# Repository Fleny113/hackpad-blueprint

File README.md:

# Fleny's Hackpad

Repo containing the files for my HackPad made for Blueprint by Hack Club.

It has a rotary encoder for volume, 4 keys for media control with an extra one for anything that might be useful and a OLED to show information about the media.

This is my first time doing any PCB and CAD work, so hopefully there isn't a mess

## BOM

- 1x Seeed Studio XIAO RP2040
- 1x 0.91 inch OLED displays
- 1x EC11 Rotary encoder
- 2x SK6812 MINI-E LEDs
- 5x MX-Style switches
- 8x M3x5mx4mm heatset inserts
- 8x M3 Screws

## Images

### Schematic

The schematic for the hackpad

### PCB

The PCB of the hackpad

<details>
<summary>PCB without the zones shown</summary>

The PCB but with the zones hidden as I find them confusing when searching the traces

</details>

### CAD

#### Entire assembly:

#### Only the body:

#### Only the lid:

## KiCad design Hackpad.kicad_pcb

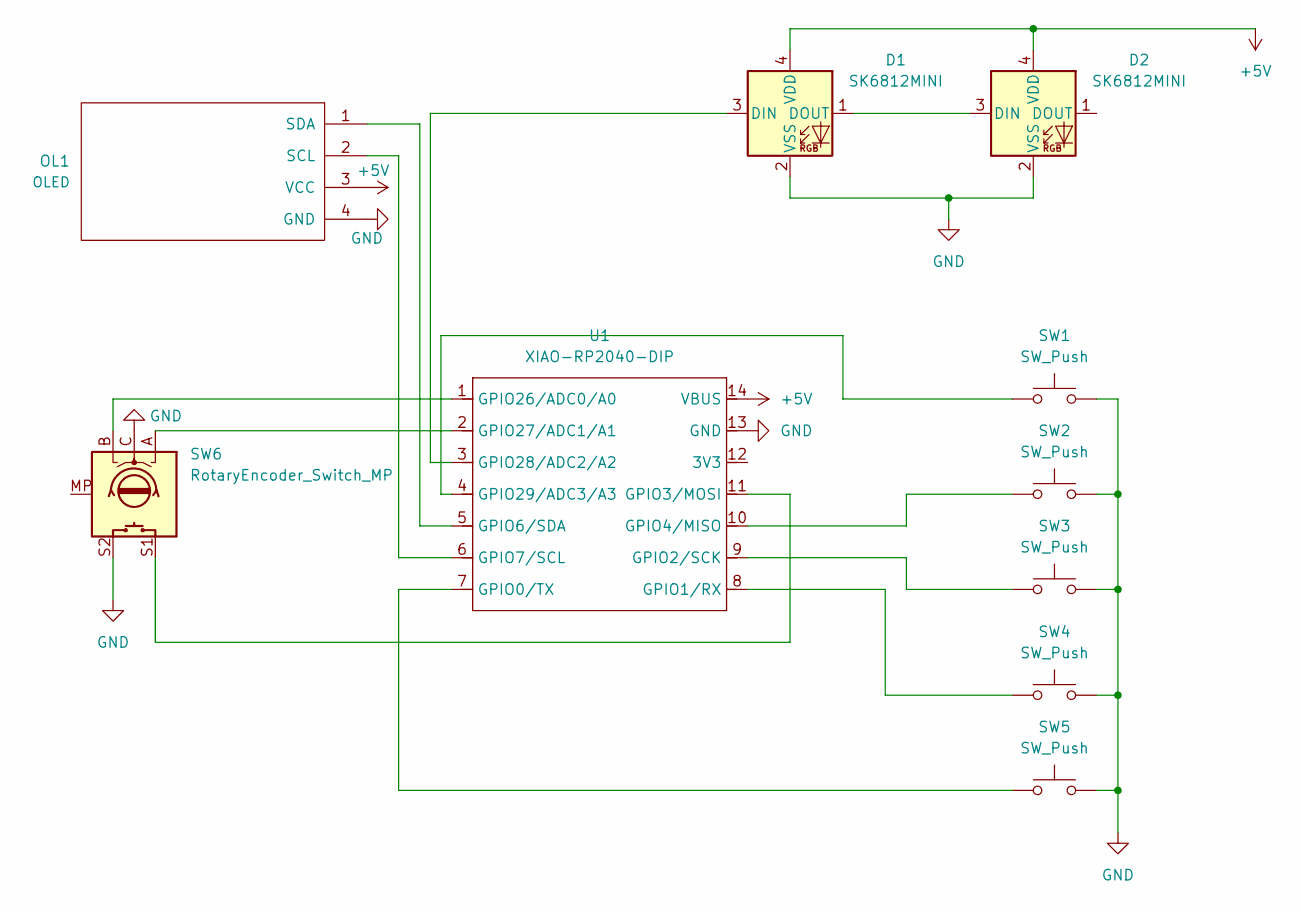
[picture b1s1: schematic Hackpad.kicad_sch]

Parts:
D1, D2: SK6812MINI; LED_SK6812MINI_PLCC4_3.5x3.5mm_P1.75mm
OL1: OLED
SW1, SW2, SW3, SW4, SW5: SW_Push; SW_Cherry_MX_PCB_1.00u
SW6: RotaryEncoder_Switch_MP; RotaryEncoder_Alps_EC11E-Switch_Vertical_H20mm_CircularMoun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
U1: XIAO-RP2040-DIP

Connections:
+5V: D1.4 (VDD), D2.4 (VDD), OL1.3 (VCC), U1.14 (VBUS)
GND: D1.2 (VSS), D2.2 (VSS), OL1.4 (GND), SW1.2, SW2.2, SW3.2, SW4.2, SW5.2, SW6.C, SW6.S2, U1.13 (GND)
unnamed: D1.3 (DIN), U1.3 (GPIO28/ADC2/A2)
unnamed: D1.1 (DOUT), D2.3 (DIN)
unnamed: OL1.2 (SCL), U1.6 (GPIO7/SCL)
unnamed: OL1.1 (SDA), U1.5 (GPIO6/SDA)
unnamed: SW5.1, U1.7 (GPIO0/TX)
unnamed: SW4.1, U1.8 (GPIO1/RX)
unnamed: SW3.1, U1.9 (GPIO2/SCK)
unnamed: SW6.S1, U1.11 (GPIO3/MOSI)
unnamed: SW2.1, U1.10 (GPIO4/MISO)
unnamed: SW6.B, U1.1 (GPIO26/ADC0/A0)
unnamed: SW6.A, U1.2 (GPIO27/ADC1/A1)
unnamed: SW1.1, U1.4 (GPIO29/ADC3/A3)

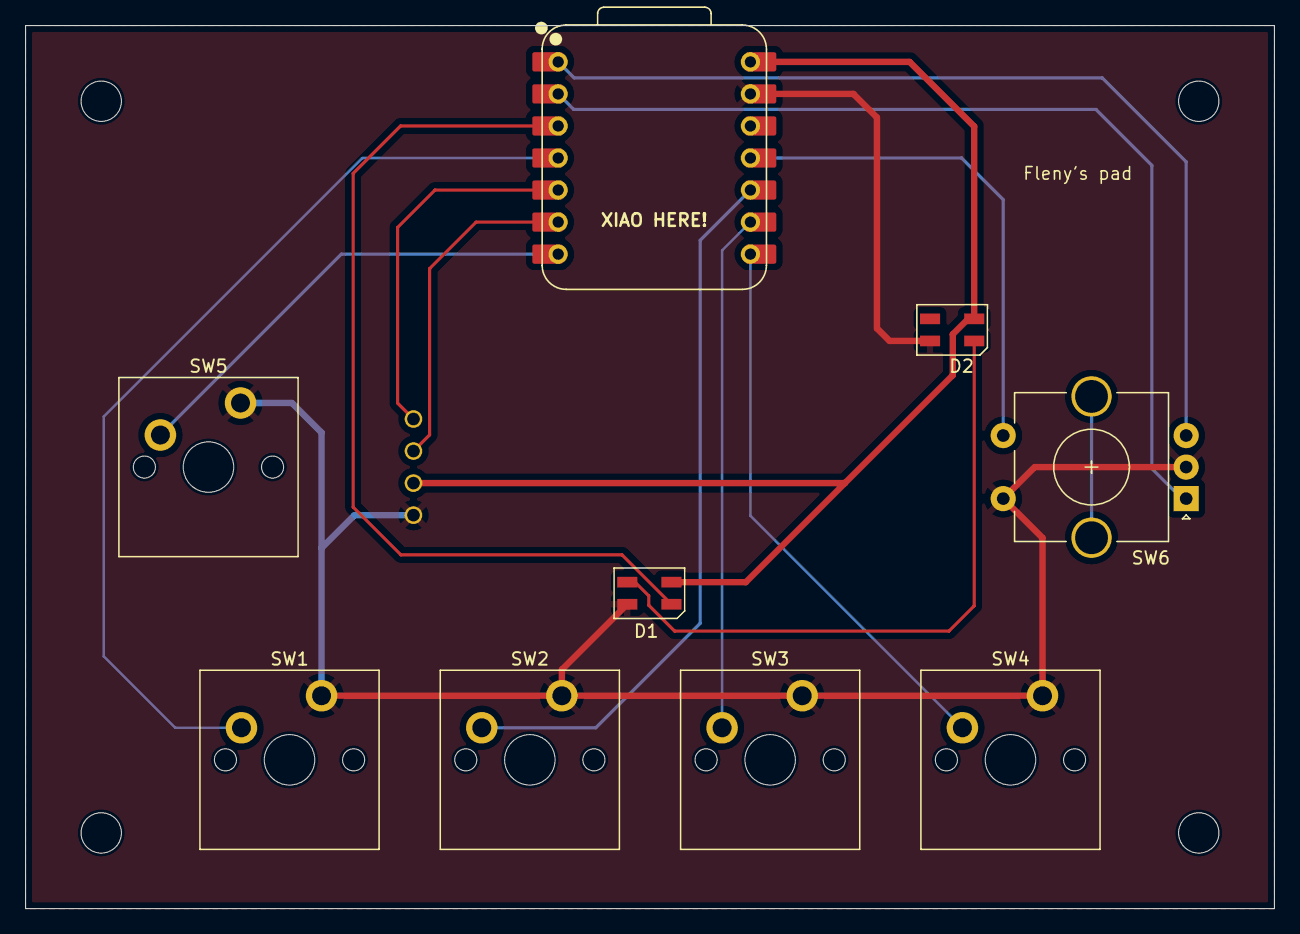
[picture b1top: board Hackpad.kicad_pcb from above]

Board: 2 copper layers, 99.0 x 70.0 mm, 10 parts (0 on the bottom side), 14 nets.

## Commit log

2025-12-28 Schematic & PCB
2025-12-28 Reroute D2 ground
2025-12-28 Add MX_V2 library
2025-12-28 Resize routes
2025-12-29 Rotate oled & reroute
2025-12-29 Center oled, SW5 and Rotary
2025-12-30 Center
2025-12-30 3D models & replace MX switch footprint
2025-12-30 Change XIAO step
2025-12-30 Add text
2025-12-30 Add README & adjust repo
2026-01-03 Fix DRC with U1 text
2026-01-03 Add fabrication files
